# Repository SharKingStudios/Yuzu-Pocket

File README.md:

# Yuzu Pocket - A PCB Business card that runs Linux!

### compact and delightfully unnecessary.

---

## Renders
*Visuals because everyone loves eye candy.*

---

## BOM
All the processors and storage sit **[here](/BOM.csv)**.

**Main characters:**
 - **Processor:** Allwinner V3LP
 - **Onboard Storage:** Winbond W25Q256JVFIQT 256Mbit SPI flash
 - **More Storage:** Micro SD Card Slot
 - **Blinken Lights:** Red and Green
- **Misc:** Boot circuitry, reset logic, pull-ups, decoupling, and other necessary magic

(See `BOM.md` for full part values, footprints, and sourcing.)

---

## What is this?

The **Yuzu Pocket** is a **Business Card that runs Linux** built around an Allwinner V3LP processor, designed to give important individuals my portfolio with some pizzazz!

It does this using its onboard USB port, integrated right into the PCB copper, to talk to the host computer. To keep things interesting, the board exposes itself as a USB gadget, giving the host multiple points of access into the board. 

## How It Works

On startup, the board will connect to the host computer and expose itself as a network device, as well as a mass storage device.

The mass storage that opens acts as the quick menu, and links the user to the more interesting parts of the project, including the hosted webpage at loganpeterson.local that exposes a shell, giving the user direct access into the device (where they can play the integrated terminal games / demos)

At a high level:

1. **The card is plugged into a USB port**
3. The V3LP boots **U-Boot and Linux**
4. Linux creates a composite USB gadget containing:
   - A small read-only help drive
   - A USB network interface
   - A serial interface
5. The host receives an address on the private USB network
6. The card advertises itself as **`loganpeterson.local`**
7. Opening the included shortcut launches a browser-based terminal
8. The visitor is now using a Linux computer thats the size of a business card

No extra special applications are required other than just having a host computer.

---

## Features

### A Real Linux Computer

Yuzu Pocket is not a microcontroller pretending to be a computer. The Allwinner V3LP contains a **32-bit ARM Cortex-A7 processor** and **64 MB of integrated DDR2 RAM**, giving the board enough room for:

- U-Boot
- A Linux kernel
- BusyBox userspace
- USB gadget services
- A web terminal
- Small native programs, games, and network demos

The firmware is intentionally based on **Buildroot** rather than a full desktop distribution.

---

### Plug-In USB Experience

The copper fingers on the edge of the PCB form a USB-A connector. Plugging the card into a computer is intended to provide both power and communication.

The Linux USB gadget configuration can expose several functions over that single connection:

- **Mass storage**
  - Shows `HOW_TO_USE.txt`
  - Includes browser shortcut files
  - Acts as the card's quick-start menu
- **USB Ethernet**
  - Creates a private network between the host and Yuzu Pocket
  - Uses `10.0.0.1` as a fallback address
- **USB serial**
  - Provides another route into the Linux console
- **Web terminal**
  - Served by [`ttyd`](https://github.com/tsl0922/ttyd)
  - Intended URL: **`http://loganpeterson.local:7681/`**

---

### Onboard Storage

Yuzu Pocket has two storage paths:

| Storage | Capacity | Purpose |
|---|---:|---|
| Winbond W25Q256 SPI NOR | 256 Mbit / 32 MB | Compact onboard firmware and persistent assets |
| microSD | Card dependent | Development, recovery, larger Linux images, and *experiments* |

The initial development image targets microSD because it is easier to rebuild and recover. The final compact image is intended to fit within the **32 MB onboard SPI NOR**, using a small kernel and compressed root filesystem.

That storage budget is tight enough to be interesting, but large enough for a fun Linux userspace.

---

### Fourteen Blinken Lights

The card includes:

- **7 red LEDs**
- **7 green LEDs**
- **14 total individually controlled channels**

The LEDs are driven through two ULN2003 Darlington transistor arrays. Linux sees them as GPIO-controlled indicators, allowing them to be used for:

- Boot progress
- Storage activity
- USB connection status
- Network activity
- Error codes
- Loading animations
- *Gratuitous blinking*

Because silent business cards are suspicious.

---

## Firmware

Firmware lives in **[`Firmware/`](/Firmware/)** and is organized as a Buildroot external tree.

The closest upstream starting point is the **Allwinner V3s / Lichee Pi Zero** support found in U-Boot and Linux. V3LP is treated as V3s-like for the initial port, with DRAM initialization being the part most likely to require V3LP-specific work.

See the **[firmware README](/Firmware/README.md)** for build commands, image layout, and current implementation details.

## What Can It Run?

The target is small native Linux software.

This includes:

- Terminal games
- LED animations
- Tiny HTTP services
- Network experiments
- My Portfolio
- A minimal Minecraft-protocol-compatible server
- Whatever fits inside the remaining storage budget

> There is an integration point reserved for [`p2r3/bareiron`](https://github.com/p2r3/bareiron), a compact C Minecraft server experiment. It is not enabled by default yet because upstream requires generated Minecraft registry data before compilation (and I havent gotten to that).

---

## Why?

The **Yuzu Pocket** exists because I wanted a portfolio piece that people would actually remember, rather than another ordinary business card or QR code printed on cardstock (though it has one too!).

It combines my interest in PCB design, embedded systems, and questionable software experiments into something small enough to carry everywhere and hand out to people.

---

## Contributing

Ideas, fixes, experiments, and constructive criticism are welcome.

- Open an issue
- Submit a pull request
- Suggest a tiny program that belongs on the card
- Improve the V3LP boot support
- Help reduce the image size
- Find a fun use for fourteen LEDs
- Make the DOOM situation worse

Please keep PCB and firmware changes clearly separated. Hardware files live in `PCB/`; firmware and build integration belong in `Firmware/`.

---

## Disclaimer

This is an open hardware and firmware project under active development.

It includes:

- Custom power regulation
- Fine-pitch PCB assembly
- USB hardware
- Boot firmware
- Flashing tools capable of overwriting storage
- Enough exposed engineering decisions to create exciting new failure modes

If you overwrite the wrong drive, short a power rail, install a component backward, or release the magic smoke, the business card will be significantly less useful at networking events.

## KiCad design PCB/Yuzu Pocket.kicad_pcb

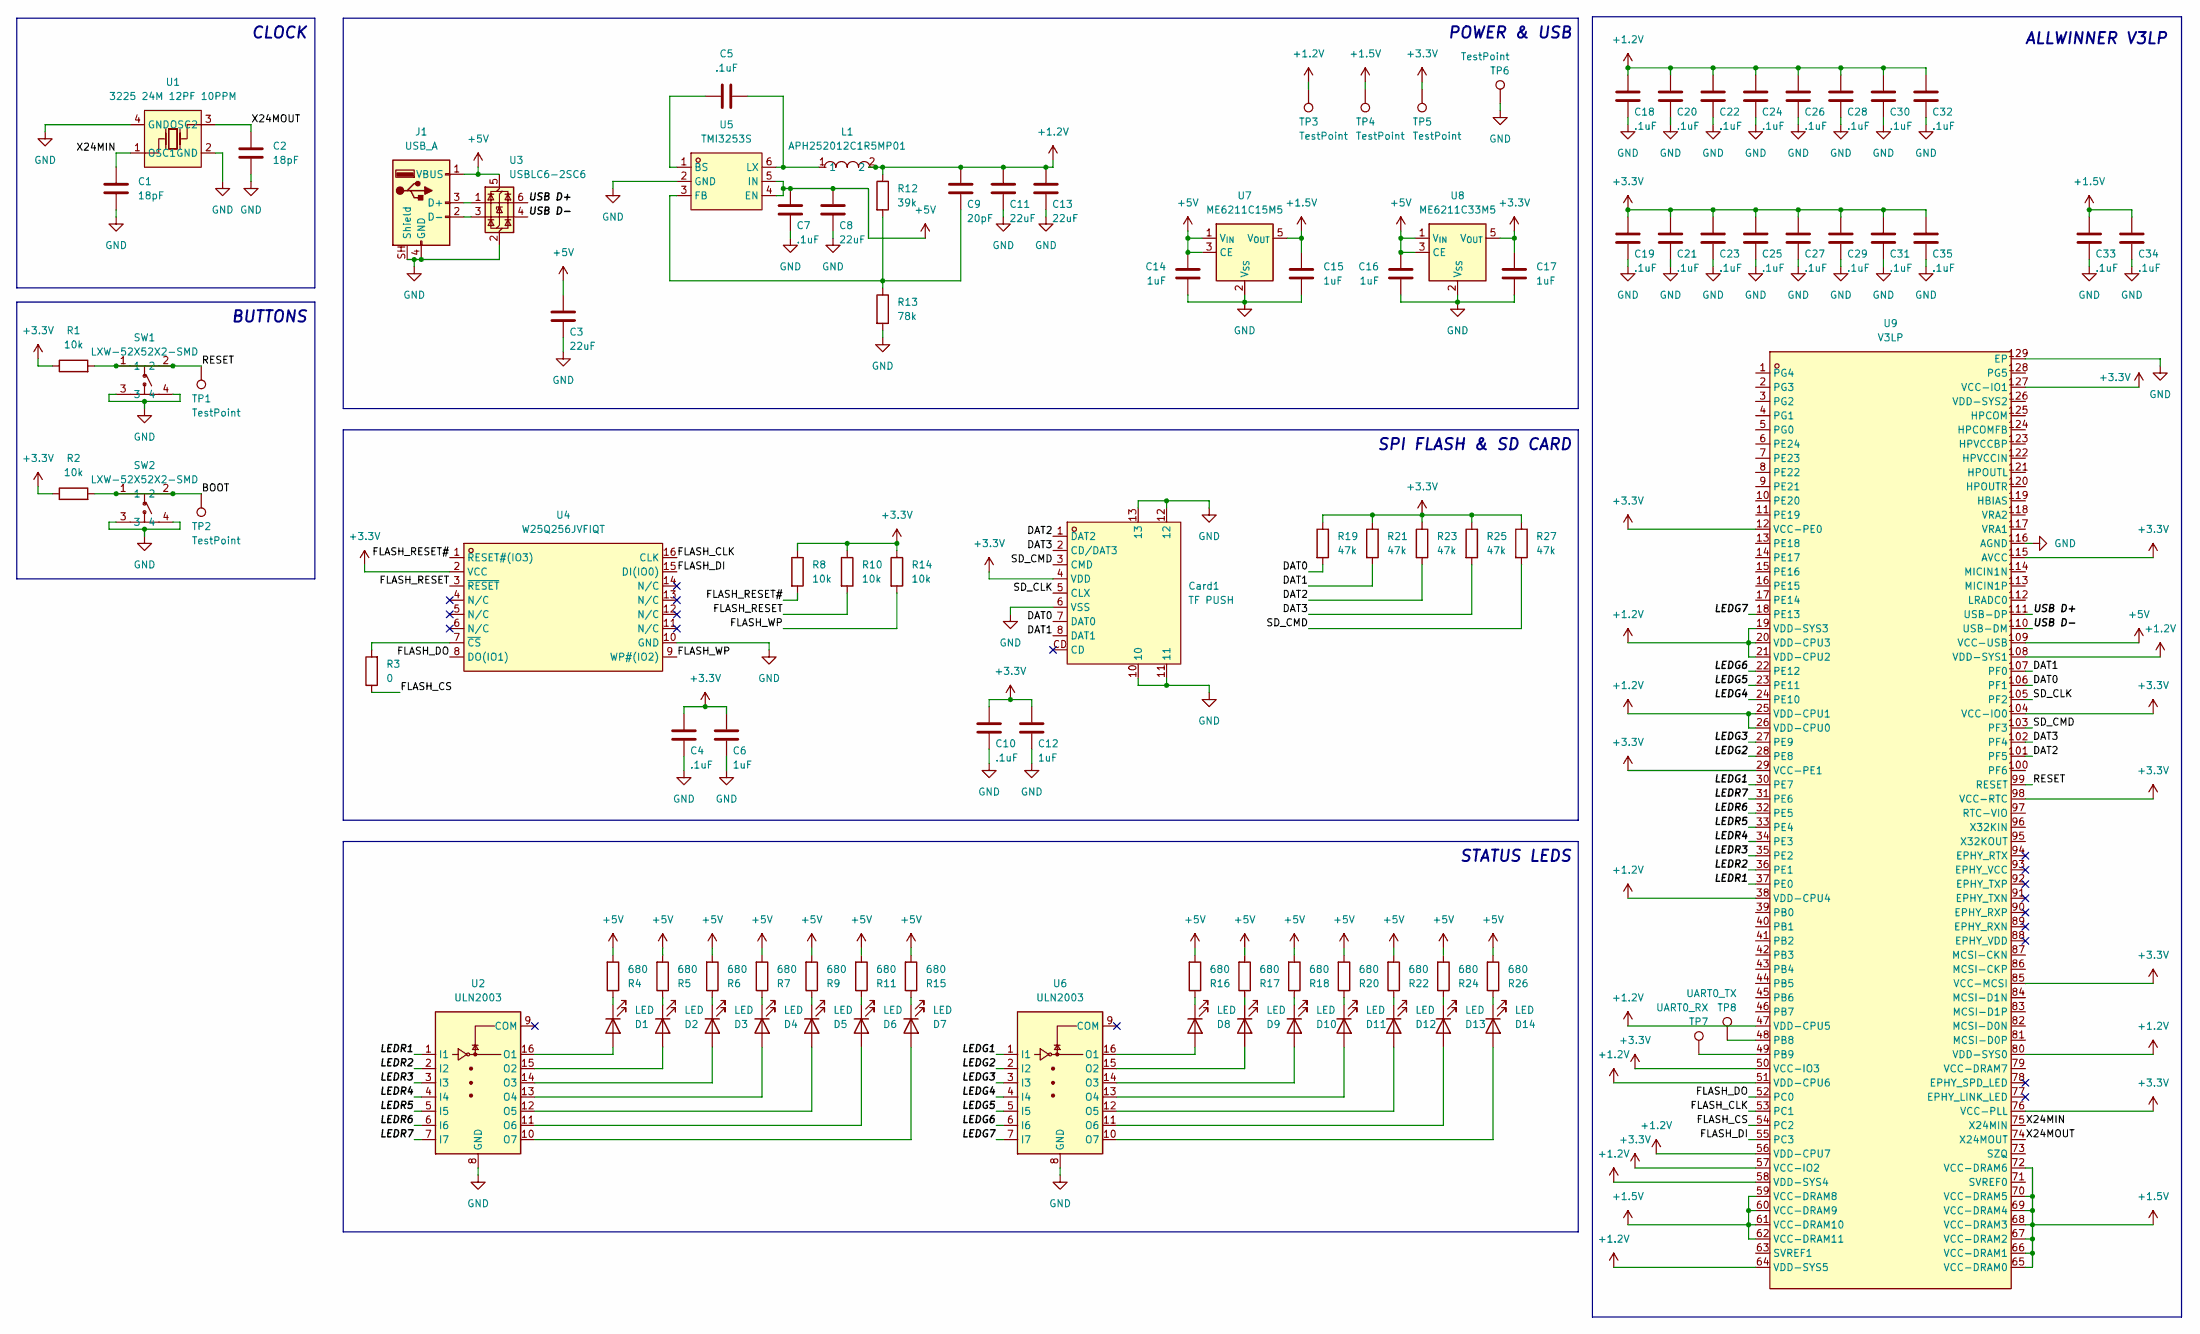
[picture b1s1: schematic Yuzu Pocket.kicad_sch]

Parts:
C1, C2: 18pF; C_0603_1608Metric_Pad1.08x0.95mm_HandSolder
C3, C8, C11, C13: 22uF; C_0603_1608Metric_Pad1.08x0.95mm_HandSolder
C4, C5, C7, C10, C18, C19, C20, C21, C22, C23, C24, C25, C26, C27, C28, C29, C30, C31, C32, C33, C34, C35: .1uF; C_0603_1608Metric_Pad1.08x0.95mm_HandSolder
C6, C12, C14, C15, C16, C17: 1uF; C_0603_1608Metric_Pad1.08x0.95mm_HandSolder
C9: 20pF; C_0603_1608Metric_Pad1.08x0.95mm_HandSolder
Card1: TF PUSH; TF-SMD_TF-PUSH; MPN TF PUSH; LCSC Part C393941
D1, D2, D3, D4, D5, D6, D7, D8, D9, D10, D11, D12, D13, D14: LED; LED_0603_1608Metric
J1: USB_A; USB_A_PCB_Edge_receptacle
L1: APH252012C1R5MP01; IND-SMD_APH252012C3R3MP01; MPN APH252012C1R5MP01; LCSC Part C42455360
R1, R2, R8, R10, R14: 10k; R_0603_1608Metric_Pad0.98x0.95mm_HandSolder
R3: 0; R_0603_1608Metric_Pad0.98x0.95mm_HandSolder
R4, R5, R6, R7, R9, R11, R15, R16, R17, R18, R20, R22, R24, R26: 680; R_0603_1608Metric_Pad0.98x0.95mm_HandSolder
R12: 39k; R_0603_1608Metric_Pad0.98x0.95mm_HandSolder
R13: 78k; R_0603_1608Metric_Pad0.98x0.95mm_HandSolder
R19, R21, R23, R25, R27: 47k; R_0603_1608Metric_Pad0.98x0.95mm_HandSolder
SW1, SW2: LXW-52X52X2-SMD; SW-SMD_4P-L5.2-W5.2-P5.80-LS6.4; MPN LXW-52X52X2-SMD; LCSC Part C53447014
TP1, TP2, TP3, TP4, TP5, TP6: TestPoint; TestPoint_Pad_D1.5mm
TP7: UART0_RX; TestPoint_Pad_D1.5mm
TP8: UART0_TX; TestPoint_Pad_D1.5mm
U1: 3225 24M 12PF 10PPM; CRYSTAL-SMD_4P-L3.2-W2.5-BL; MPN 3225 24M 12PF 10PPM; LCSC Part C5181479
U2, U6: ULN2003; SOIC-16_3.9x9.9mm_P1.27mm
U3: USBLC6-2SC6; SOT-23-6
U4: W25Q256JVFIQT; SOIC-16_L10.3-W7.5-P1.27-LS10.3-BL; MPN W25Q256JVFIQ; LCSC Part C779876
U5: TMI3253S; SOT-23-6_L2.9-W1.6-P0.95-LS2.8-BL; MPN TMI3253S; LCSC Part C478943
U7: ME6211C15M5; SOT-23-5
U8: ME6211C33M5; SOT-23-5
U9: V3LP; LQFP-128_L14.0-W14.0-P0.40-LS16.0-BL-EP5.6; MPN V3LP; LCSC Part C5350798

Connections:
+1.2V: C9.2, C11.2, C13.2, C18.2, C20.2, C22.2, C24.2, C26.2, C28.2, C30.2, C32.2, L1.2, R12.1, TP3.1 (1_1), U9.19 (VDD-SYS3), U9.20 (VDD-CPU3), U9.21 (VDD-CPU2), U9.25 (VDD-CPU1), U9.26 (VDD-CPU0), U9.38 (VDD-CPU4), U9.47 (VDD-CPU5), U9.51 (VDD-CPU6), U9.56 (VDD-CPU7), U9.58 (VDD-SYS4), U9.64 (VDD-SYS5), U9.80 (VDD-SYS0), U9.108 (VDD-SYS1)
+1.5V: C15.1, C33.2, C34.2, TP4.1 (1_1), U7.5 (V_{OUT}), U9.59 (VCC-DRAM8), U9.60 (VCC-DRAM9), U9.61 (VCC-DRAM10), U9.62 (VCC-DRAM11), U9.65 (VCC-DRAM0), U9.66 (VCC-DRAM1), U9.67 (VCC-DRAM2), U9.68 (VCC-DRAM3), U9.69 (VCC-DRAM4), U9.70 (VCC-DRAM5), U9.72 (VCC-DRAM6)
+3.3V: C4.2, C6.2, C10.2, C12.2, C17.1, C19.2, C21.2, C23.2, C25.2, C27.2, C29.2, C31.2, C35.2, Card1.4 (VDD), R1.1, R2.1, R8.1, R10.1, R14.1, R19.1, R21.1, R23.1, R25.1, R27.1, TP5.1 (1_1), U4.2 (VCC), U8.5 (V_{OUT}), U9.12 (VCC-PE0), U9.29 (VCC-PE1), U9.50 (VCC-IO3), U9.57 (VCC-IO2), U9.76 (VCC-PLL), U9.85 (VCC-MCSI), U9.98 (VCC-RTC), U9.104 (VCC-IO0), U9.115 (AVCC), U9.127 (VCC-IO1)
+5V: C3.2, C7.2, C8.2, C14.2, C16.2, J1.1 (VBUS), R4.2, R5.2, R6.2, R7.2, R9.2, R11.2, R15.2, R16.2, R17.2, R18.2, R20.2, R22.2, R24.2, R26.2, U3.5 (VBUS), U5.4 (EN), U5.5 (IN), U7.1 (V_{IN}), U7.3 (CE), U8.1 (V_{IN}), U8.3 (CE), U9.109 (VCC-USB)
/DAT0: Card1.7 (DAT0), R19.2, U9.106 (PF1)
/DAT1: Card1.8 (DAT1), R21.2, U9.107 (PF0)
/DAT2: Card1.1 (DAT2), R23.2, U9.101 (PF5)
/DAT3: Card1.2 (CD/DAT3), R25.2, U9.102 (PF4)
/FLASH_CLK: U4.16 (CLK), U9.53 (PC1)
/FLASH_CS: R3.1, U9.54 (PC2)
/FLASH_DI: U4.15 (DI(IO0)), U9.55 (PC3)
/FLASH_DO: U4.8 (DO(IO1)), U9.52 (PC0)
/FLASH_RESET: R10.2, U4.3 (~RESET)
/FLASH_RESET#: R8.2, U4.1 (RESET#(IO3))
/FLASH_WP: R14.2, U4.9 (WP#(IO2))
/LEDG1: U6.1 (I1), U9.30 (PE7)
/LEDG2: U6.2 (I2), U9.28 (PE8)
/LEDG3: U6.3 (I3), U9.27 (PE9)
/LEDG4: U6.4 (I4), U9.24 (PE10)
/LEDG5: U6.5 (I5), U9.23 (PE11)
/LEDG6: U6.6 (I6), U9.22 (PE12)
/LEDG7: U6.7 (I7), U9.18 (PE13)
/LEDR1: U2.1 (I1), U9.37 (PE0)
/LEDR2: U2.2 (I2), U9.36 (PE1)
/LEDR3: U2.3 (I3), U9.35 (PE2)
/LEDR4: U2.4 (I4), U9.34 (PE3)
/LEDR5: U2.5 (I5), U9.33 (PE4)
/LEDR6: U2.6 (I6), U9.32 (PE5)
/LEDR7: U2.7 (I7), U9.31 (PE6)
/RESET: R1.2, SW1.1, SW1.2, TP1.1 (1_1), U9.99 (RESET)
/SD_CLK: Card1.5 (CLX), U9.105 (PF2)
/SD_CMD: Card1.3 (CMD), R27.2, U9.103 (PF3)
/USB D+: U3.6 (I/O1), U9.111 (USB-DP)
/USB D-: U3.4 (I/O2), U9.110 (USB-DM)
/X24MIN: C1.1, U1.1 (OSC1), U9.75 (X24MIN)
/X24MOUT: C2.1, U1.3 (OSC2), U9.74 (X24MOUT)
GND: C1.2, C2.2, C3.1, C4.1, C6.1, C7.1, C8.1, C10.1, C11.1, C12.1, C13.1, C14.1, C15.2, C16.1, C17.2, C18.1, C19.1, C20.1, C21.1, C22.1, C23.1, C24.1, C25.1, C26.1, C27.1, C28.1, C29.1, C30.1, C31.1, C32.1, C33.1, C34.1, C35.1, Card1.6 (VSS), Card1.10, Card1.11, Card1.12, Card1.13, J1.4 (GND), J1.SH (Shield), R13.2, SW1.3, SW1.4, SW2.3, SW2.4, TP6.1 (1_1), U1.2 (GND), U1.4 (GND), U2.8 (GND), U3.2 (GND), U4.10 (GND), U5.2 (GND), U6.8 (GND), U7.2 (V_{SS}), U8.2 (V_{SS}), U9.116 (AGND), U9.129 (EP)
unnamed: D1.2 (A), U2.16 (O1)
unnamed: D1.1 (K), R4.1
unnamed: D2.2 (A), U2.15 (O2)
unnamed: D2.1 (K), R5.1
unnamed: D3.2 (A), U2.14 (O3)
unnamed: D3.1 (K), R6.1
unnamed: D4.2 (A), U2.13 (O4)
unnamed: D4.1 (K), R7.1
unnamed: D5.2 (A), U2.12 (O5)
unnamed: D5.1 (K), R9.1
unnamed: D6.2 (A), U2.11 (O6)
unnamed: D6.1 (K), R11.1
unnamed: D7.2 (A), U2.10 (O7)
unnamed: D7.1 (K), R15.1
unnamed: D8.2 (A), U6.16 (O1)
unnamed: D8.1 (K), R16.1
unnamed: D9.2 (A), U6.15 (O2)
unnamed: D9.1 (K), R17.1
unnamed: D10.2 (A), U6.14 (O3)
unnamed: D10.1 (K), R18.1
unnamed: D11.2 (A), U6.13 (O4)
unnamed: D11.1 (K), R20.1
unnamed: D12.2 (A), U6.12 (O5)
unnamed: D12.1 (K), R22.1
unnamed: D13.2 (A), U6.11 (O6)
unnamed: D13.1 (K), R24.1
unnamed: D14.2 (A), U6.10 (O7)
unnamed: D14.1 (K), R26.1
unnamed: J1.3 (D+), U3.1 (I/O1)
unnamed: J1.2 (D-), U3.3 (I/O2)
unnamed: R2.2, SW2.1, SW2.2, TP2.1
unnamed: R3.2, U4.7 (~CS)
unnamed: C5.1, U5.1 (BS)
unnamed: C9.1, R12.2, R13.1, U5.3 (FB)
unnamed: C5.2, L1.1, U5.6 (LX)
unnamed: TP8.1 (1_1), U9.48 (PB8)
unnamed: TP7.1 (1_1), U9.49 (PB9)

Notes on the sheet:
BUTTONS
CLOCK
ALLWINNER V3LP
POWER & USB
SPI FLASH & SD CARD
STATUS LEDS

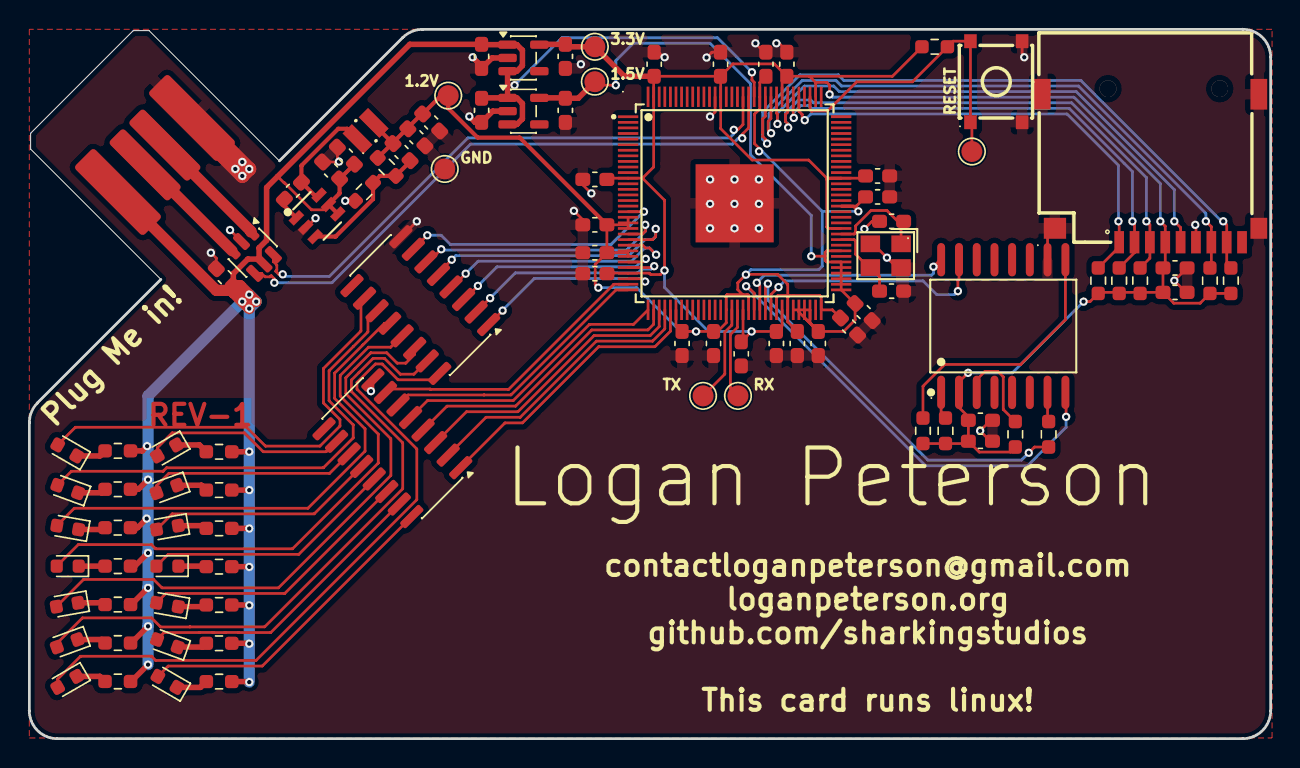
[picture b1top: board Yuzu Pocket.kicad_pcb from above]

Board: 2 copper layers, 88.9 x 50.8 mm, 95 parts (0 on the bottom side), 73 nets.

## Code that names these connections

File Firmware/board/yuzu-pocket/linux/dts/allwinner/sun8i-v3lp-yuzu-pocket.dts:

// SPDX-License-Identifier: (GPL-2.0+ OR MIT)
/*
 * Yuzu Pocket business-card Linux board.
 *
 * V3LP is treated as V3s-compatible for this first firmware target.
 * Confirmed board differences from Lichee Pi Zero are captured here.
 */

/dts-v1/;
#include "sun8i-v3s.dtsi"
#include "sunxi-common-regulators.dtsi"
#include <dt-bindings/gpio/gpio.h>

/ {
	model = "Yuzu Pocket V3LP";
	compatible = "yuzu,yuzu-pocket-v3lp", "allwinner,sun8i-v3s";

	aliases {
		serial0 = &uart0;
		mmc0 = &mmc0;
		spi0 = &spi0;
	};

	chosen {
		stdout-path = "serial0:115200n8";
		bootargs = "console=ttyS0,115200 earlycon root=/dev/mmcblk0p2 rootwait rw panic=5";
	};

	memory@40000000 {
		device_type = "memory";
		reg = <0x40000000 0x04000000>;
	};

	leds {
		compatible = "gpio-leds";

		red1 {
			label = "yuzu:red:1";
			gpios = <&pio 4 0 GPIO_ACTIVE_HIGH>; /* PE0 */
		};

		red2 {
			label = "yuzu:red:2";
			gpios = <&pio 4 1 GPIO_ACTIVE_HIGH>; /* PE1 */
		};

		red3 {
			label = "yuzu:red:3";
			gpios = <&pio 4 2 GPIO_ACTIVE_HIGH>; /* PE2 */
		};

		red4 {
			label = "yuzu:red:4";
			gpios = <&pio 4 3 GPIO_ACTIVE_HIGH>; /* PE3 */
		};

		red5 {
			label = "yuzu:red:5";
			gpios = <&pio 4 4 GPIO_ACTIVE_HIGH>; /* PE4 */
		};

		red6 {
			label = "yuzu:red:6";
			gpios = <&pio 4 5 GPIO_ACTIVE_HIGH>; /* PE5 */
		};

		red7 {
			label = "yuzu:red:7";
			gpios = <&pio 4 6 GPIO_ACTIVE_HIGH>; /* PE6 */
		};

		green1 {
			label = "yuzu:green:1";
			gpios = <&pio 4 7 GPIO_ACTIVE_HIGH>; /* PE7 */
		};

		green2 {
			label = "yuzu:green:2";
			gpios = <&pio 4 8 GPIO_ACTIVE_HIGH>; /* PE8 */
		};

		green3 {
			label = "yuzu:green:3";
			gpios = <&pio 4 9 GPIO_ACTIVE_HIGH>; /* PE9 */
		};

		green4 {
			label = "yuzu:green:4";
			gpios = <&pio 4 10 GPIO_ACTIVE_HIGH>; /* PE10 */
		};

		green5 {
			label = "yuzu:green:5";
			gpios = <&pio 4 11 GPIO_ACTIVE_HIGH>; /* PE11 */
		};

		green6 {
			label = "yuzu:green:6";
			gpios = <&pio 4 12 GPIO_ACTIVE_HIGH>; /* PE12 */
		};

		green7 {
			label = "yuzu:green:7";
			gpios = <&pio 4 13 GPIO_ACTIVE_HIGH>; /* PE13 */
		};
	};
};

&mmc0 {
	broken-cd;
	bus-width = <4>;
	vmmc-supply = <&reg_vcc3v3>;
	status = "okay";
};

&spi0 {
	pinctrl-0 = <&spi0_pins>;
	pinctrl-names = "default";
	status = "okay";

	flash@0 {
		compatible = "jedec,spi-nor";
		reg = <0>;
		spi-max-frequency = <50000000>;
	};
};

&uart0 {
	pinctrl-0 = <&uart0_pb_pins>;
	pinctrl-names = "default";
	status = "okay";
};

&usb_otg {
	dr_mode = "peripheral";
	status = "okay";
};

&usbphy {
	status = "okay";
};

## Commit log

2026-06-09 Selected Processor
    Selected the Allwinner V3LP as the main processor for the board and started some of the schematic for that.
2026-06-10 Schematic done!
2026-06-10 PCB Layout + Routing Done
    The business card is ready for silkscreen!
2026-06-12 firmware + zine page
2026-06-12 Added BOM
2026-06-13 Updated Gerbers to V1.1 and Fleshed out README
2026-06-13 Add Zine to README
